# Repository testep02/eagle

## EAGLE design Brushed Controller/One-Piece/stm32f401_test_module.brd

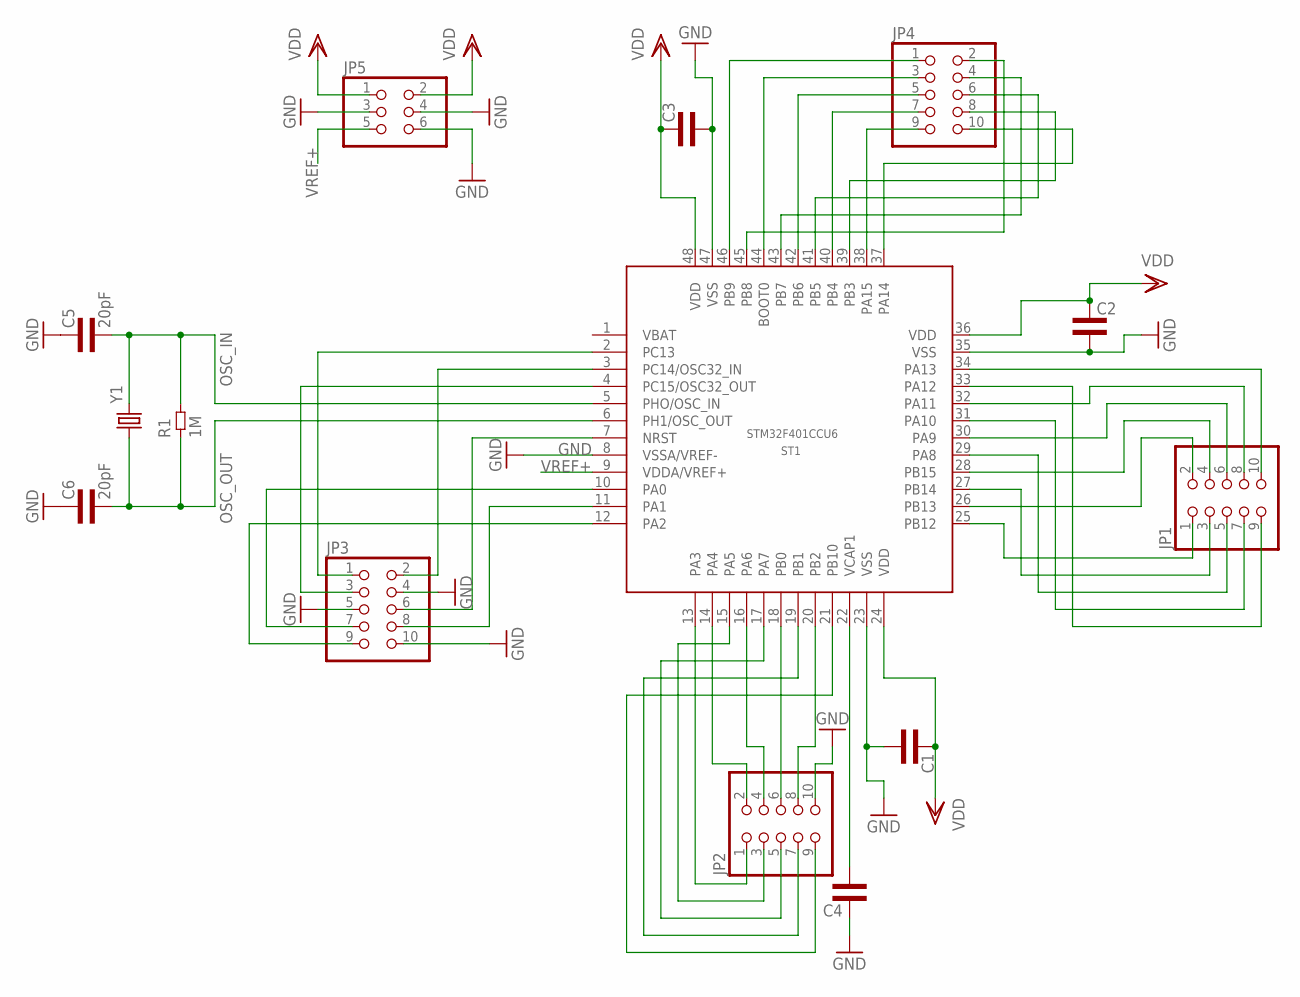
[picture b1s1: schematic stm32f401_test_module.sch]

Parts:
C1, C2, C3, C4: CAP0402L3; 0402L3
C5, C6: 20pF; 0603L3
JP1, JP2, JP3, JP4: PINHD-2X5; 2X05
JP5: PINHD-2X3; 2X03
R1: 1M; 0603L3
ST1: STM32F401CCU6; UFQFPN48
Y1: CRYSTALHC49US; HC49US

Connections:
GND: C1.P$2 (2), C2.P$2 (2), C3.P$2 (2), C4.P$1 (1), C5.P$1 (1), C6.P$1 (1), JP2.10, JP3.4, JP3.5, JP3.10, JP5.3, JP5.4, JP5.6, ST1.8 (VSSA/VREF-), ST1.23 (VSS), ST1.35 (VSS), ST1.47 (VSS)
unnamed: JP2.7, ST1.19 (PB1)
unnamed: JP2.8, ST1.20 (PB2)
unnamed: JP2.9, ST1.21 (PB10)
unnamed: C4.P$2 (2), ST1.22 (VCAP1)
unnamed: JP3.1, ST1.2 (PC13)
unnamed: JP3.2, ST1.3 (PC14/OSC32_IN)
unnamed: JP3.3, ST1.4 (PC15/OSC32_OUT)
unnamed: JP3.6, ST1.7 (NRST)
unnamed: JP3.7, ST1.10 (PA0)
unnamed: JP3.8, ST1.11 (PA1)
unnamed: JP3.9, ST1.12 (PA2)
unnamed: JP2.1, ST1.13 (PA3)
unnamed: JP2.2, ST1.14 (PA4)
unnamed: JP2.3, ST1.15 (PA5)
unnamed: JP2.4, ST1.16 (PA6)
unnamed: JP2.5, ST1.17 (PA7)
unnamed: JP2.6, ST1.18 (PB0)
unnamed: JP1.1, ST1.25 (PB12)
unnamed: JP1.2, ST1.26 (PB13)
unnamed: JP1.3, ST1.27 (PB14)
unnamed: JP1.4, ST1.28 (PB15)
unnamed: JP1.5, ST1.29 (PA8)
unnamed: JP1.6, ST1.30 (PA9)
unnamed: JP1.7, ST1.31 (PA10)
unnamed: JP1.8, ST1.32 (PA11)
unnamed: JP1.9, ST1.33 (PA12)
unnamed: JP1.10, ST1.34 (PA13)
unnamed: JP4.1, ST1.46 (PB9)
unnamed: JP4.2, ST1.45 (PB8)
unnamed: JP4.3, ST1.44 (BOOT0)
unnamed: JP4.4, ST1.43 (PB7)
unnamed: JP4.5, ST1.42 (PB6)
unnamed: JP4.6, ST1.41 (PB5)
unnamed: JP4.7, ST1.40 (PB4)
unnamed: JP4.8, ST1.39 (PB3)
unnamed: JP4.9, ST1.38 (PA15)
unnamed: JP4.10, ST1.37 (PA14)
OSC_IN: C5.P$2 (2), R1.P$2 (2), ST1.5 (PHO/OSC_IN), Y1.2
OSC_OUT: C6.P$2 (2), R1.P$1 (1), ST1.6 (PH1/OSC_OUT), Y1.1
VDD: C1.P$1 (1), C2.P$1 (1), C3.P$1 (1), JP5.1, JP5.2, ST1.24 (VDD), ST1.36 (VDD), ST1.48 (VDD)
VREF+: JP5.5, ST1.9 (VDDA/VREF+)

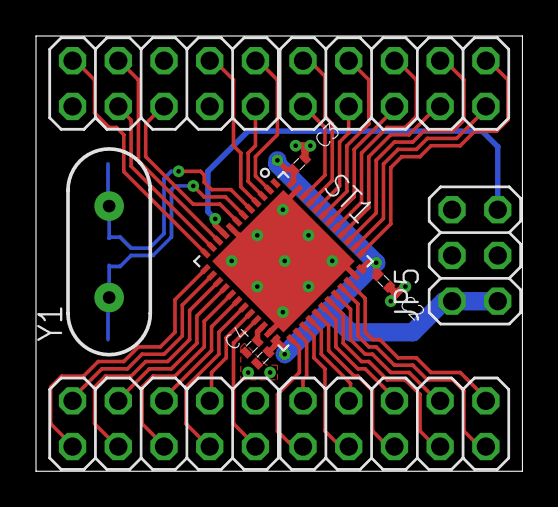
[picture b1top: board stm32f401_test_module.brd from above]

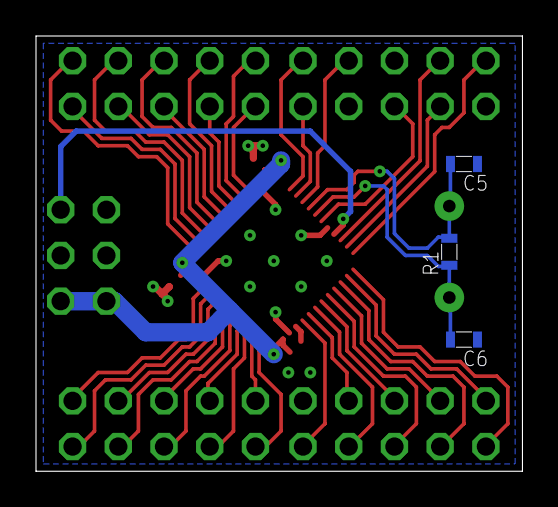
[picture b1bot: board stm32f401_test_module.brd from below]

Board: 2 copper layers, 27.0 x 24.2 mm, 14 parts (3 on the bottom side), 42 nets.

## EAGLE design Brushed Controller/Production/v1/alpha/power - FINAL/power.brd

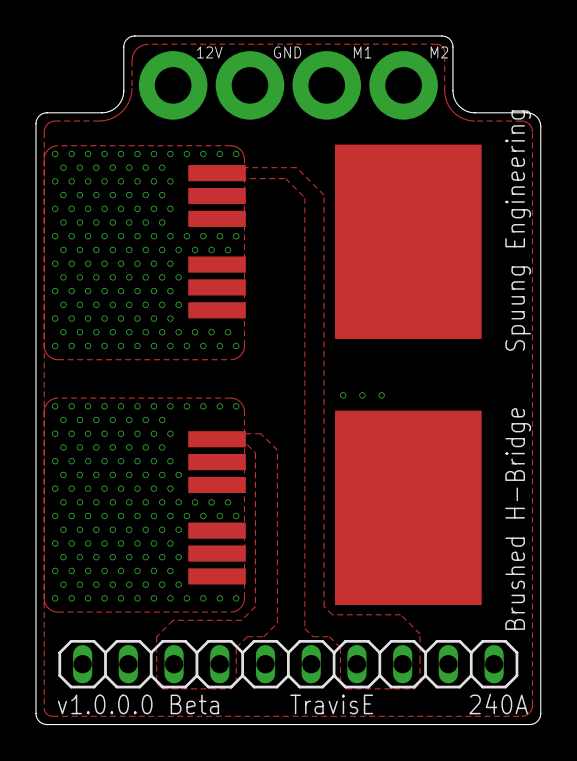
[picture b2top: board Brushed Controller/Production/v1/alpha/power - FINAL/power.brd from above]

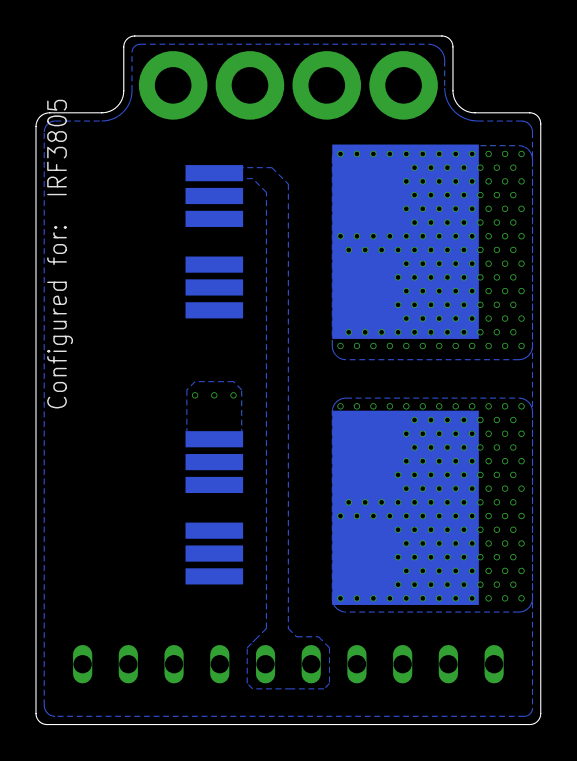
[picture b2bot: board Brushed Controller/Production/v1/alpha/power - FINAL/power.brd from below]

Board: 4 copper layers, 28.0 x 38.3 mm, 5 parts (2 on the bottom side), 8 nets, no tracks yet.

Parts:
JP1: 1X10
U$1, U$2, U$3, U$4: IRF3805STRL-7PP; D2PAK-7

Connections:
12V: U$1.8, U$2.8
GND: U$3.2, U$3.3, U$3.5, U$3.6, U$3.7, U$4.2, U$4.3, U$4.5, U$4.6, U$4.7
HO1: JP1.7, JP1.8, U$1.1
HO2: JP1.3, JP1.4, U$2.1
LO1: JP1.5, JP1.6, U$3.1
LO2: JP1.1, JP1.2, U$4.1
M1: JP1.10, U$1.2, U$1.3, U$1.5, U$1.6, U$1.7, U$3.8
M2: JP1.9, U$2.2, U$2.3, U$2.5, U$2.6, U$2.7, U$4.8

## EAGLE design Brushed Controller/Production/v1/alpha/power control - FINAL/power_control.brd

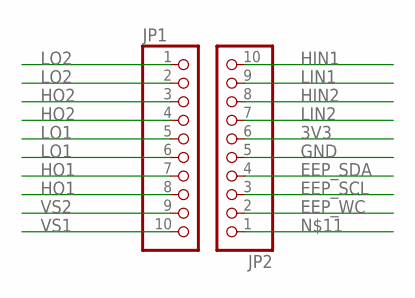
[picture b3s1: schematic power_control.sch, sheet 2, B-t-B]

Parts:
JP1, JP2: PINHD-1X10_2.54-SMD; 1X10SMD

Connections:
3V3: JP2.6; also elsewhere on the board
EEP_SCL: JP2.3; also elsewhere on the board
EEP_SDA: JP2.4; also elsewhere on the board
EEP_WC: JP2.2; also elsewhere on the board
GND: JP2.5; also elsewhere on the board
HIN1: JP2.10; also elsewhere on the board
HIN2: JP2.8; also elsewhere on the board
HO1: JP1.7, JP1.8; also elsewhere on the board
HO2: JP1.3, JP1.4; also elsewhere on the board
LIN1: JP2.9; also elsewhere on the board
LIN2: JP2.7; also elsewhere on the board
LO1: JP1.5, JP1.6; also elsewhere on the board
LO2: JP1.1, JP1.2; also elsewhere on the board
VS1: JP1.10; also elsewhere on the board
VS2: JP1.9; also elsewhere on the board

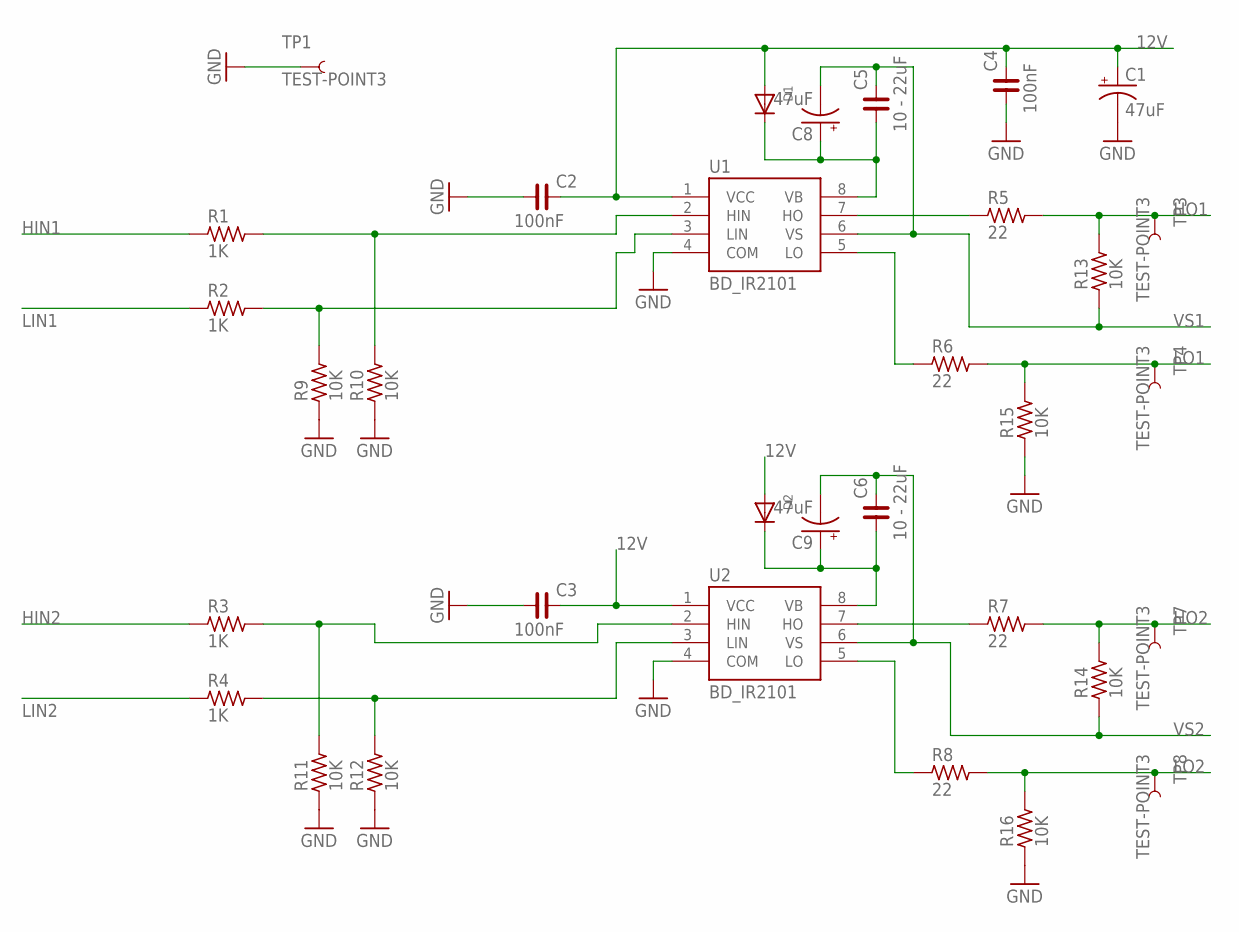
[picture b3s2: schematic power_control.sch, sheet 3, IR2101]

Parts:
C1, C8, C9: 47uF; B/3528-21W
C2, C3, C4: 100nF; C0201
C5, C6: 10 - 22uF; C0805
D1, D2: DIODESOD-523; SOD-523
R1, R2, R3, R4: 1K; R0201
R5, R6, R7, R8: 22; R0805
R9, R10, R11, R12: 10K; R0201
R13, R14, R15, R16: 10K; R0805
TP1, TP3, TP4, TP7, TP8: TEST-POINT3; PAD.03X.03
U1, U2: BD_IR2101; SO8

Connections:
12V: C1.+, C2.2, C3.2, C4.2, D1.A, D2.A, U1.1 (VCC), U2.1 (VCC)
GND: C1.-, C2.1, C3.1, C4.1, R9.1, R10.1, R11.1, R12.1, R15.1, R16.1, TP1.P$1, U1.4 (COM), U2.4 (COM); also elsewhere on the board
HIN1: R1.1; also elsewhere on the board
HIN2: R3.1; also elsewhere on the board
HO1: R5.2, R13.2, TP3.P$1; also elsewhere on the board
HO2: R7.2, R14.2, TP7.P$1; also elsewhere on the board
LIN1: R2.1; also elsewhere on the board
LIN2: R4.1; also elsewhere on the board
LO1: R6.2, R15.2, TP4.P$1; also elsewhere on the board
LO2: R8.2, R16.2, TP8.P$1; also elsewhere on the board
unnamed: C6.1, C9.+, D2.K (C), U2.8 (VB)
unnamed: C5.1, C8.+, D1.K (C), U1.8 (VB)
unnamed: R1.2, R10.2, U1.2 (HIN)
unnamed: R2.2, R9.2, U1.3 (LIN)
unnamed: R5.1, U1.7 (HO)
unnamed: R6.1, U1.5 (LO)
unnamed: R3.2, R11.2, U2.2 (HIN)
unnamed: R4.2, R12.2, U2.3 (LIN)
unnamed: R7.1, U2.7 (HO)
unnamed: R8.1, U2.5 (LO)
VS1: C5.2, C8.-, R13.1, U1.6 (VS); also elsewhere on the board
VS2: C6.2, C9.-, R14.1, U2.6 (VS); also elsewhere on the board

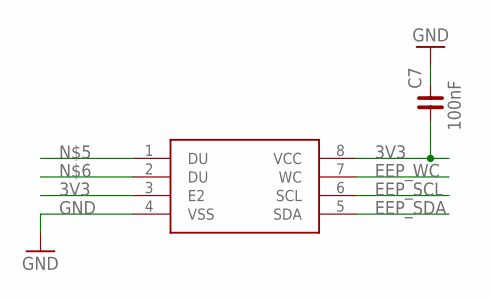
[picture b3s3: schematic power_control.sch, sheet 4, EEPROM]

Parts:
C7: 100nF; C0201
M24M02: M24M02-DRMN6TP; SO08

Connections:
3V3: C7.1, M24M02.3 (E2), M24M02.8 (VCC); also elsewhere on the board
EEP_SCL: M24M02.6 (SCL); also elsewhere on the board
EEP_SDA: M24M02.5 (SDA); also elsewhere on the board
EEP_WC: M24M02.7 (WC); also elsewhere on the board
GND: C7.2, M24M02.4 (VSS); also elsewhere on the board

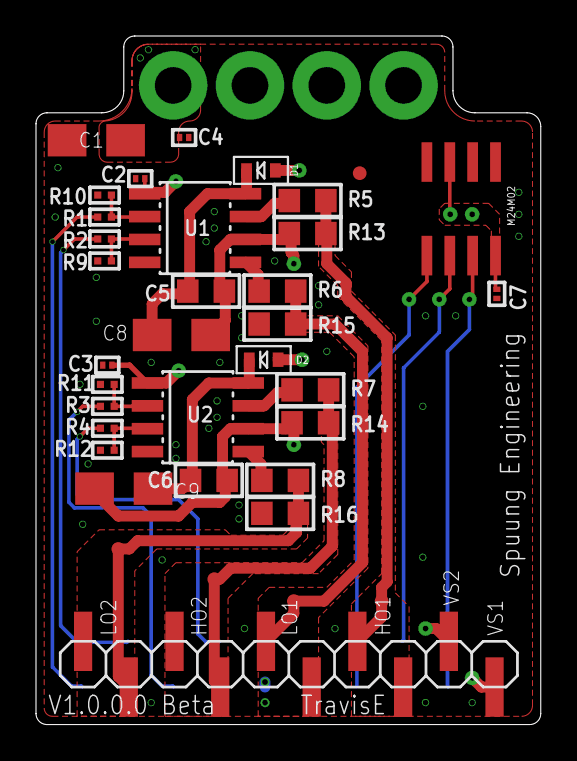
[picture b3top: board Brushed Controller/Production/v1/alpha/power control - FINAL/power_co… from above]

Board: 4 copper layers, 28.0 x 38.3 mm, 37 parts (1 on the bottom side), 26 nets.

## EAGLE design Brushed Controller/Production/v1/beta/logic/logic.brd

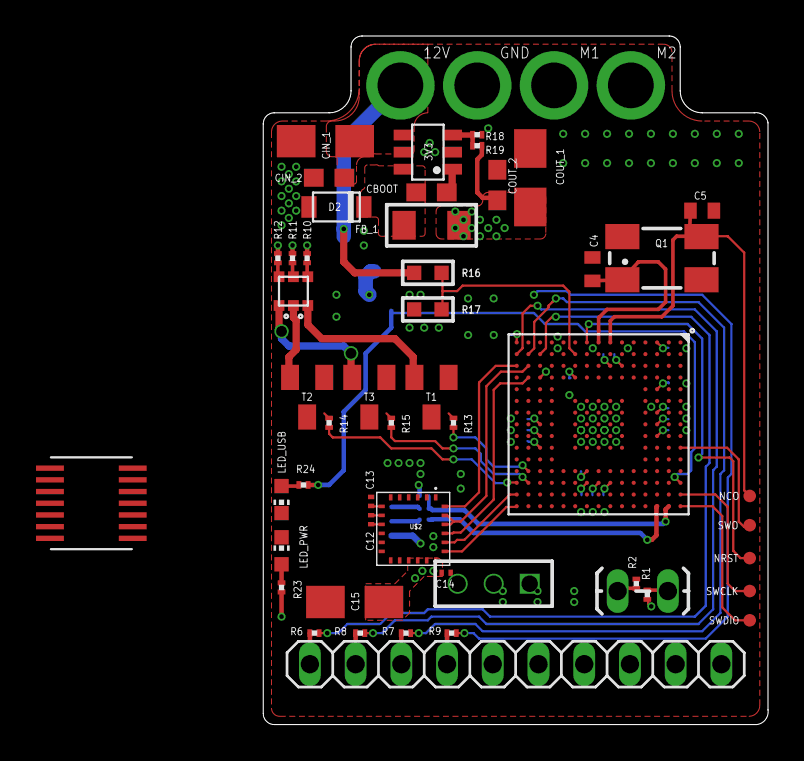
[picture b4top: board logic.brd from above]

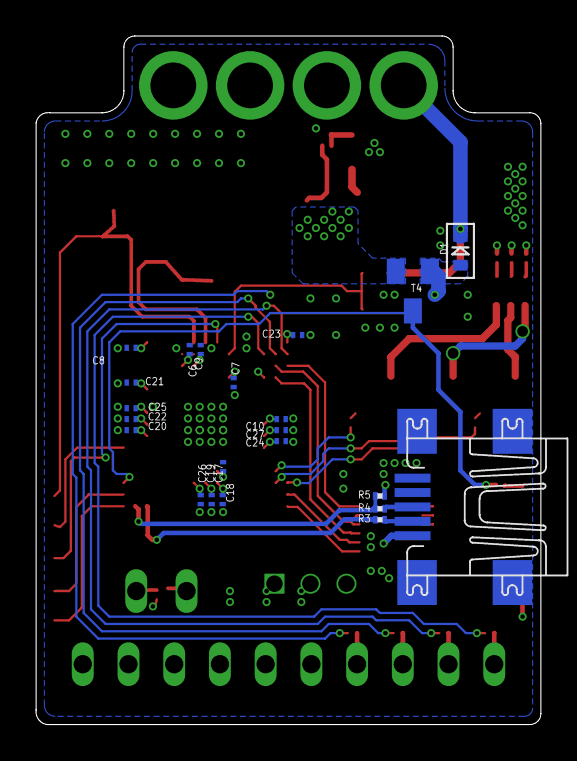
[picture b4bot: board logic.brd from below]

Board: 4 copper layers, 28.0 x 38.3 mm, 72 parts (22 on the bottom side), 51 nets.

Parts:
3V3: LMR14206; R-PDSO-G6
C4, C5: 20p; C0402
C6, C7, C8, C9, C10, C17, C18, C19, C20, C21, C22, C23, C24, C25, C26, C27: 100n; C0201
C12: .22uF; C0201
C13: 4.7uF; C0201
C14: 100nF; C0201
C15: 10uF; B/3528-21W
CBOOT: .15uF; C0603
CIN_1: 10uF; B/3528-21W
CIN_2: 100nF; C0603
COUT_1: 47uF; B/3528-21W
COUT_2: 100nF; C0603
D1: SOD-523
D2: DB2W60400L; SC-109B
FB_1: FB_1206; L1206
JP1: M02LOCK_LONGPADS; 1X02_LOCK_LONGPADS
JP2: 1X03M
JP3: 1X10
LED1: LED_RGB3; RGBLED
LED_PWR: CHIP-LED0603
LED_USB: CHIP-LED0603
NCO: TPTP07R; TP07R
NRST: TPTP07R; TP07R
Q1: CTS406
R1, R10, R11, R12, R13, R14, R15: 100; R0201
R2: 10K; R0201
R3, R4, R6, R7, R8, R9: 22; R0201
R5: 1.5K; R0201
R16, R17: R0603
R18: 1.02K; R0201
R19: 3.4K; R0201
R23, R24: 330; R0201
SWCLK: TPTP07R; TP07R
SWDIO: TPTP07R; TP07R
SWO: TPTP07R; TP07R
T1, T2, T3, T4: SOT23-BEC
U1: R-PDSO-G14
U$2: LSM9DS0; LGA-24
U$6: STM32F407IG; UFBGA176+25
X1: MINI-USB-UX60A-MB-5ST; UX60A-MB-5ST

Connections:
3V3: 3V3.6, CBOOT.2, D2.1, FB_1.1
+12V: 3V3.4, 3V3.5, CIN_1.+, CIN_2.1, D1.K, R16.2
GND: 3V3.2, C4.2, C5.2, C6.2, C7.2, C8.2, C9.2, C10.2, C13.1, C14.1, C15.-, C17.2, C18.2, C19.2, C20.2, C21.2, C22.2, C23.2, C24.2, C25.2, C26.2, C27.2, CIN_1.-, CIN_2.2, COUT_1.-, COUT_2.2, D2.2, JP2.3, LED_PWR.C, LED_USB.C, R2.2, R17.1, R18.1, T1.E, T2.E, T3.E, U$2.2, U$2.3, U$2.4, U$2.5, U$2.6, U$6.D5, U$6.D7, U$6.D8, U$6.D9, U$6.F2, U$6.F6, U$6.F7, U$6.F8, U$6.F9, U$6.F10, U$6.F12, U$6.G2, U$6.G6, U$6.G7, U$6.G8, U$6.G9, U$6.G10, U$6.G12, U$6.H6, U$6.H7, U$6.H8, U$6.H9, U$6.H10, U$6.H12, U$6.J6, U$6.J7, U$6.J8, U$6.J9, U$6.J10, U$6.K6, U$6.K7, U$6.K8, U$6.K9, U$6.K10, U$6.M1, U$6.M8, U$6.M9, X1.5
HIN1: JP3.1, R6.2
HIN2: JP3.3, R7.2
LED_BLUE: R15.2, U$6.P13
LED_GREEN: R13.2, U$6.P12
LED_RED: R14.2, U$6.R13
LIN1: JP3.2, R8.2
LIN2: JP3.4, R9.2
LIPO_ADC_SIG: R16.1, R17.2, U$6.K2
unnamed: JP1.1, R1.2
unnamed: R13.1, T1.B
unnamed: R14.1, T2.B
unnamed: R15.1, T3.B
unnamed: LED1.AR, R11.2
unnamed: LED1.CR, T2.C
unnamed: 3V3.1, CBOOT.1
unnamed: JP1.2, R2.1
unnamed: R3.1, X1.2
unnamed: 3V3.3, R18.2, R19.2
unnamed: R4.1, X1.3
unnamed: C13.2, U$2.7
unnamed: C12.1, U$2.8
unnamed: LED1.CG, T1.C
unnamed: LED1.AG, R10.2
unnamed: LED1.CB, T3.C
unnamed: LED1.AB, R12.2
unnamed: C12.2, U$2.9
unnamed: LED_PWR.A, R23.1
unnamed: LED_USB.A, R24.2
NRST: NRST.TP, U$6.J1
OSC_IN: C5.1, NCO.TP, Q1.3, U$6.G1
OSC_OUT: C4.1, Q1.1, U$6.H1
PA3: R8.1, U$6.R2
PA4: R9.1, U$6.N4
PB14: U$2.20, U$6.R14
PB15: U$2.19, U$6.R15
PWM_1: R6.1, U$6.N2
PWM_2: R7.1, U$6.P2
SPI1_MISO: U$2.22, U$2.23, U$6.P3
SPI1_MOSI: U$2.24, U$6.R3
SPI1_SCK: U$2.21, U$6.P4
SWCLK: SWCLK.TP, U$6.A14
SWDIO: SWDIO.TP, U$6.A15
SWO: SWO.TP, U$6.A10
USB_DETECT: R24.1, T4.C, U$6.A13
USB_DETECT_TRANS: D1.A, T4.B, X1.1
USB_DM: R3.2, U$6.C15
USB_DP: R4.2, R5.1, U$6.B15
VDD: C6.1, C7.1, C8.1, C9.1, C10.1, C14.2, C15.+, C17.1, C18.1, C19.1, C20.1, C21.1, C22.1, C23.1, C24.1, C25.1, C26.1, C27.1, COUT_1.+, COUT_2.1, FB_1.2, JP2.2, R1.1, R5.2, R10.1, R11.1, R12.1, R19.1, R23.2, T4.E, U$2.15, U$2.16, U$2.17, U$2.18, U$6.C1, U$6.C5, U$6.C7, U$6.C8, U$6.C9, U$6.F3, U$6.G3, U$6.G13, U$6.H13, U$6.J12, U$6.J13, U$6.K4, U$6.N8, U$6.N9, U$6.N10, U$6.R1

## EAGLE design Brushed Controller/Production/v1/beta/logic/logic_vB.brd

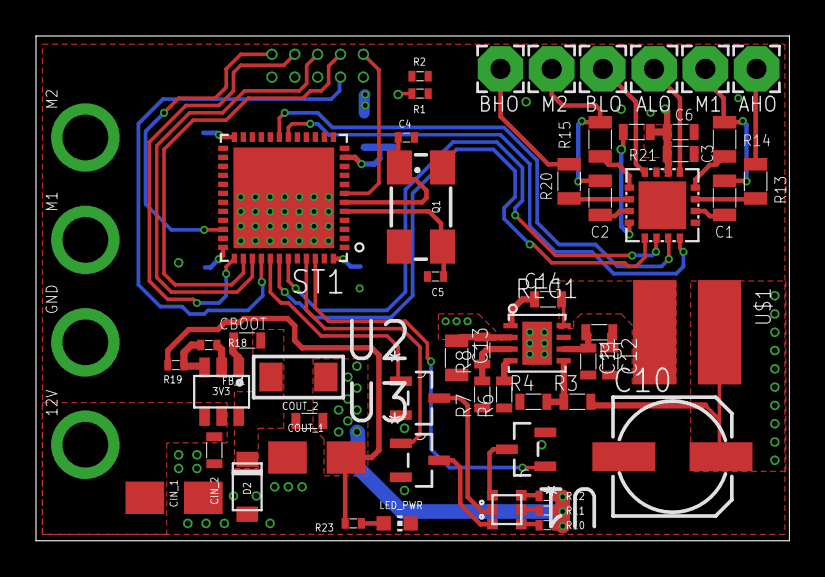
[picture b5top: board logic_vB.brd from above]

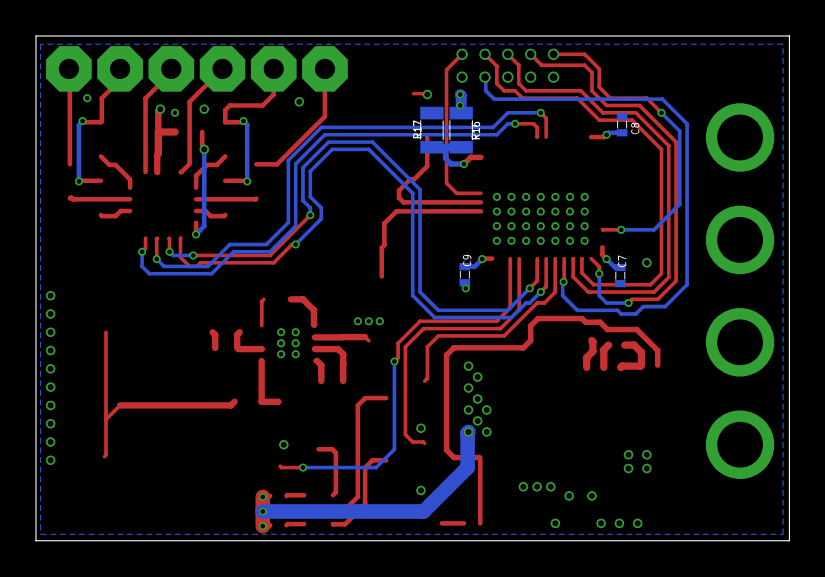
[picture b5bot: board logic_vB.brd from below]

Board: 4 copper layers, 41.9 x 28.0 mm, 59 parts (5 on the bottom side), 44 nets.

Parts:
3V3: LMR14206; R-PDSO-G6
AHO: 2,54/1,1
ALO: 2,54/1,1
BHO: 2,54/1,1
BLO: 2,54/1,1
C1, C2: 10u; 0805L3
C3: 1u; 0603L3
C4, C5: 20p; 0402L3
C6: 10u; 0603L3
C7, C8, C9: 100n; 0402L3
C10: 153CLV-0605
C11, C12, C14: 0603L3
C13: 0805L3
CBOOT: .15uF; 0603L3
CIN_1: 10uF; B/3528-21W
CIN_2: 100nF; 0603L3
COUT_1: 47uF; B/3528-21W
COUT_2: 100nF; 0603L3
D2: DB2W60400L; SC-109B
FB_1: FB_1206; L1206
LED1: LED_RGB3; RGBLED
LED_PWR: CHIP-LED0603
M1, M2: 2,54/1,1
MD1: QFN44-16LD-PL-2
Q1: CTS406
R1: 100; 0402L3
R2: 10K; 0402L3
R3, R4, R5, R6, R7, R8: 0603L3
R10, R23: 330; 0402L3
R11: 1K; 0402L3
R12: 510; 0402L3
R13, R20: 10R; 0805L3
R14, R15: 2R; 0805L3
R16, R17: 0805L3
R18: 1.02K; 0402L3
R19: 3.4K; 0402L3
R21: 100K; 0603L3
REG1: S-PVSON-N8
ST1: UFQFPN48
U1, U2, U3: BC817-25; SOT95P240X97-3N
U$1: SDR0604

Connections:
3V3: 3V3.6, CBOOT.P$2, D2.1, FB_1.1
+12V: 3V3.4, 3V3.5, C13.1, CIN_1.+, CIN_2.P$1, R8.P$2, R16.2, REG1.2
AB: LED1.AB, R12.P$2
AG: LED1.AG, R10.P$2
AHO: AHO.1, R13.2
ALO: ALO.1, MD1.5
AR: LED1.AR, R11.P$2
BHO: BHO.1, R20.2
BLO: BLO.1, MD1.8
BOOT: C14.P$1, REG1.1
COMP: C11.P$1, R5.P$2, REG1.6
EN: R7.P$2, R8.P$1, REG1.3
GND: 3V3.2, C3.P$1, C4.P$2, C5.P$2, C6.P$1, C7.P$2, C8.P$2, C9.P$2, C10.-, C11.P$2, C12.P$2, C13.2, CIN_1.-, CIN_2.P$2, COUT_1.-, COUT_2.P$2, D2.2, LED_PWR.C, MD1.7, MD1.TP, R2.P$2, R4.P$1, R6.P$1, R7.P$1, R17.1, R18.P$1, REG1.7, REG1.P$1, ST1.23, ST1.35, ST1.47, U1.2, U2.2, U3.2
LED_BLUE: ST1.16, ST1.46, U1.1
LED_GREEN: ST1.15, ST1.45, U3.1
LED_RED: ST1.41, U2.1
LIPO_ADC_SIG: R16.1, R17.2, ST1.11
M1: C1.1, M1.1, R14.2
M2: C2.1, M2.1, R15.2
unnamed: C1.2, MD1.2
unnamed: C2.2, MD1.11
unnamed: MD1.3, R13.1
unnamed: 3V3.1, CBOOT.P$1
unnamed: MD1.4, R14.1
unnamed: MD1.9, R15.1
unnamed: MD1.10, R20.1
unnamed: 3V3.3, R18.P$2, R19.P$2
unnamed: LED1.CG, U3.3
unnamed: LED1.CR, U2.3
unnamed: LED1.CB, U1.3
unnamed: C12.P$1, R5.P$1
unnamed: LED_PWR.A, R23.P$1
unnamed: MD1.12, R21.P$1
OSC_IN: C5.P$1, Q1.3, ST1.5
OSC_OUT: C4.P$1, Q1.1, ST1.6
PH: C14.P$2, REG1.8, U$1.2
PWM_1: MD1.16, ST1.18
PWM_2: MD1.15, ST1.19
PWM_3: MD1.13, ST1.42
PWM_4: MD1.14, ST1.43
RT: R6.P$2, REG1.4
VCC: C3.P$2, C6.P$2, C10.+, MD1.6, R3.P$2, R21.P$2, U$1.1
VDD: C7.P$1, C8.P$1, C9.P$1, COUT_1.+, COUT_2.P$1, FB_1.2, R1.P$1, R10.P$1, R11.P$1, R12.P$1, R19.P$1, R23.P$2, ST1.24, ST1.36, ST1.48
VSENSE: R3.P$1, R4.P$2, REG1.5

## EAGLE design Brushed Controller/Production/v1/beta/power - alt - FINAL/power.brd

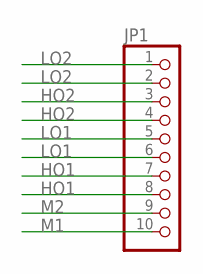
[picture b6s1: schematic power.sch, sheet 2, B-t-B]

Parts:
JP1: PINHD-1X10_2.54; 1X10

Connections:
HO1: JP1.7, JP1.8; also elsewhere on the board
HO2: JP1.3, JP1.4; also elsewhere on the board
LO1: JP1.5, JP1.6; also elsewhere on the board
LO2: JP1.1, JP1.2; also elsewhere on the board
M1: JP1.10; also elsewhere on the board
M2: JP1.9; also elsewhere on the board

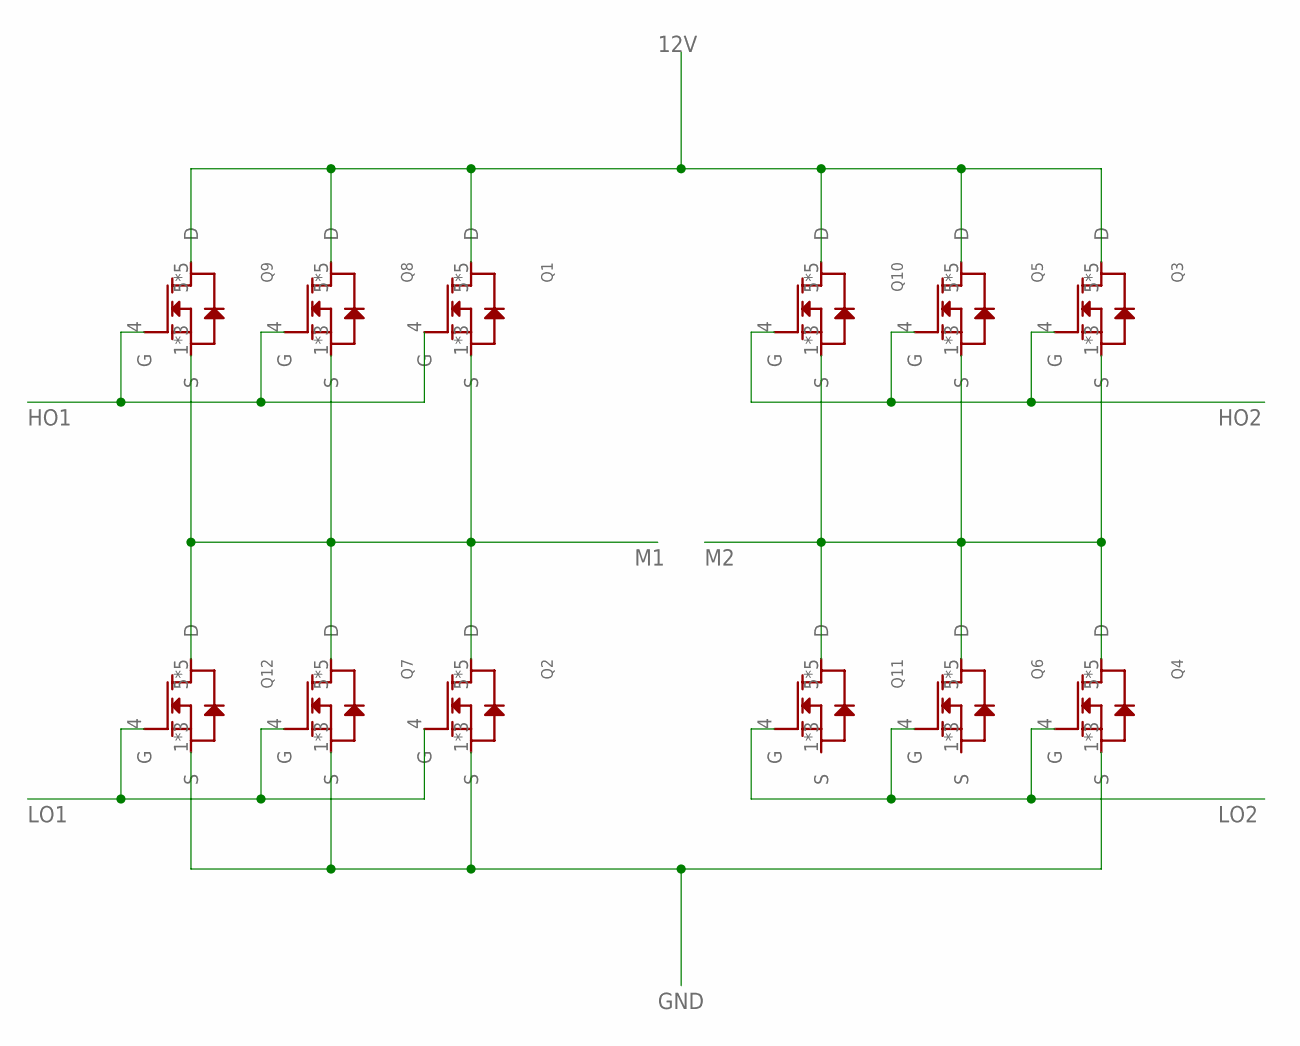
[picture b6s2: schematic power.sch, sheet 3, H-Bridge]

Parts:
Q1, Q2, Q3, Q4, Q5, Q6, Q7, Q8, Q9, Q10, Q11, Q12: CSD18540Q5B; Q5B

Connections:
12V: Q1.5 (D), Q1.6 (D), Q1.7 (D), Q1.8 (D), Q1.9 (D), Q3.5 (D), Q3.6 (D), Q3.7 (D), Q3.8 (D), Q3.9 (D), Q5.5 (D), Q5.6 (D), Q5.7 (D), Q5.8 (D), Q5.9 (D), Q8.5 (D), Q8.6 (D), Q8.7 (D), Q8.8 (D), Q8.9 (D), Q9.5 (D), Q9.6 (D), Q9.7 (D), Q9.8 (D), Q9.9 (D), Q10.5 (D), Q10.6 (D), Q10.7 (D), Q10.8 (D), Q10.9 (D)
GND: Q2.1 (S), Q2.2 (S), Q2.3 (S), Q4.1 (S), Q4.2 (S), Q4.3 (S), Q7.1 (S), Q7.2 (S), Q7.3 (S), Q12.1 (S), Q12.2 (S), Q12.3 (S)
HO1: Q1.4 (G), Q8.4 (G), Q9.4 (G); also elsewhere on the board
HO2: Q3.4 (G), Q5.4 (G), Q10.4 (G); also elsewhere on the board
LO1: Q2.4 (G), Q7.4 (G), Q12.4 (G); also elsewhere on the board
LO2: Q4.4 (G), Q6.4 (G), Q11.4 (G); also elsewhere on the board
M1: Q1.1 (S), Q1.2 (S), Q1.3 (S), Q2.5 (D), Q2.6 (D), Q2.7 (D), Q2.8 (D), Q2.9 (D), Q7.5 (D), Q7.6 (D), Q7.7 (D), Q7.8 (D), Q7.9 (D), Q8.1 (S), Q8.2 (S), Q8.3 (S), Q9.1 (S), Q9.2 (S), Q9.3 (S), Q12.5 (D), Q12.6 (D), Q12.7 (D), Q12.8 (D), Q12.9 (D); also elsewhere on the board
M2: Q3.1 (S), Q3.2 (S), Q3.3 (S), Q4.5 (D), Q4.6 (D), Q4.7 (D), Q4.8 (D), Q4.9 (D), Q5.1 (S), Q5.2 (S), Q5.3 (S), Q6.5 (D), Q6.6 (D), Q6.7 (D), Q6.8 (D), Q6.9 (D), Q10.1 (S), Q10.2 (S), Q10.3 (S), Q11.5 (D), Q11.6 (D), Q11.7 (D), Q11.8 (D), Q11.9 (D); also elsewhere on the board

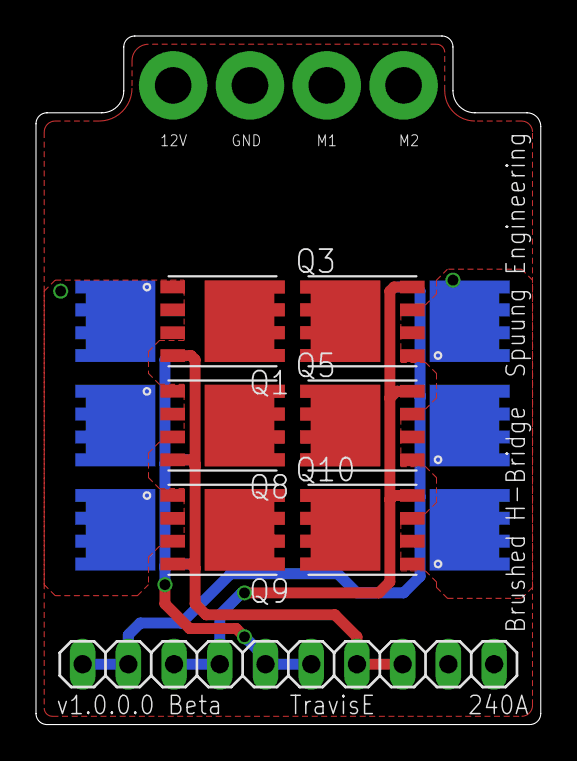
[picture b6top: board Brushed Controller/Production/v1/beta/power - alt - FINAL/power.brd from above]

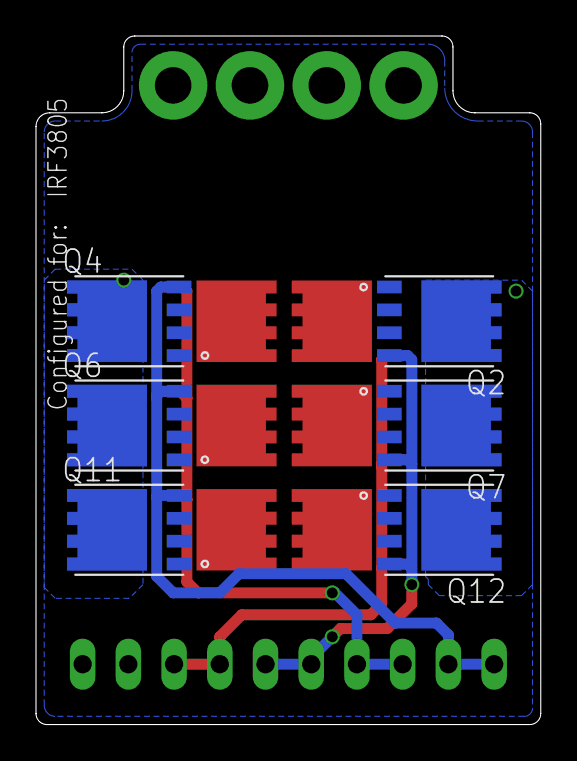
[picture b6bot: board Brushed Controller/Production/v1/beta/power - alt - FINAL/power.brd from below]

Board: 4 copper layers, 28.0 x 38.3 mm, 13 parts (6 on the bottom side), 8 nets.

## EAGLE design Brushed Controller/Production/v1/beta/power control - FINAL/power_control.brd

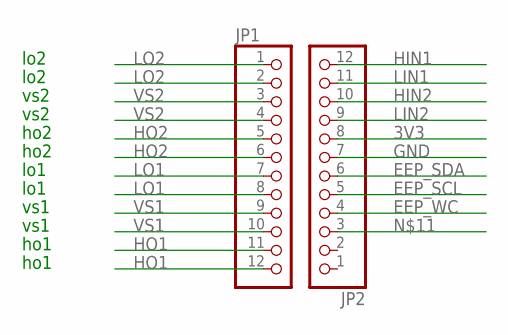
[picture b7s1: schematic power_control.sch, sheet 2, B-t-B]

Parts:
JP1, JP2: PINHD-1X12_2.54-SMD; 1X12SMD

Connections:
3V3: JP2.8; also elsewhere on the board
EEP_SCL: JP2.5; also elsewhere on the board
EEP_SDA: JP2.6; also elsewhere on the board
EEP_WC: JP2.4; also elsewhere on the board
GND: JP2.7; also elsewhere on the board
HIN1: JP2.12; also elsewhere on the board
HIN2: JP2.10; also elsewhere on the board
HO1: JP1.11, JP1.12; also elsewhere on the board
HO2: JP1.5, JP1.6; also elsewhere on the board
LIN1: JP2.11; also elsewhere on the board
LIN2: JP2.9; also elsewhere on the board
LO1: JP1.7, JP1.8; also elsewhere on the board
LO2: JP1.1, JP1.2; also elsewhere on the board
VS1: JP1.9, JP1.10; also elsewhere on the board
VS2: JP1.3, JP1.4; also elsewhere on the board

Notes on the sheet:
lo2
vs2
ho2
lo1
vs1
ho1

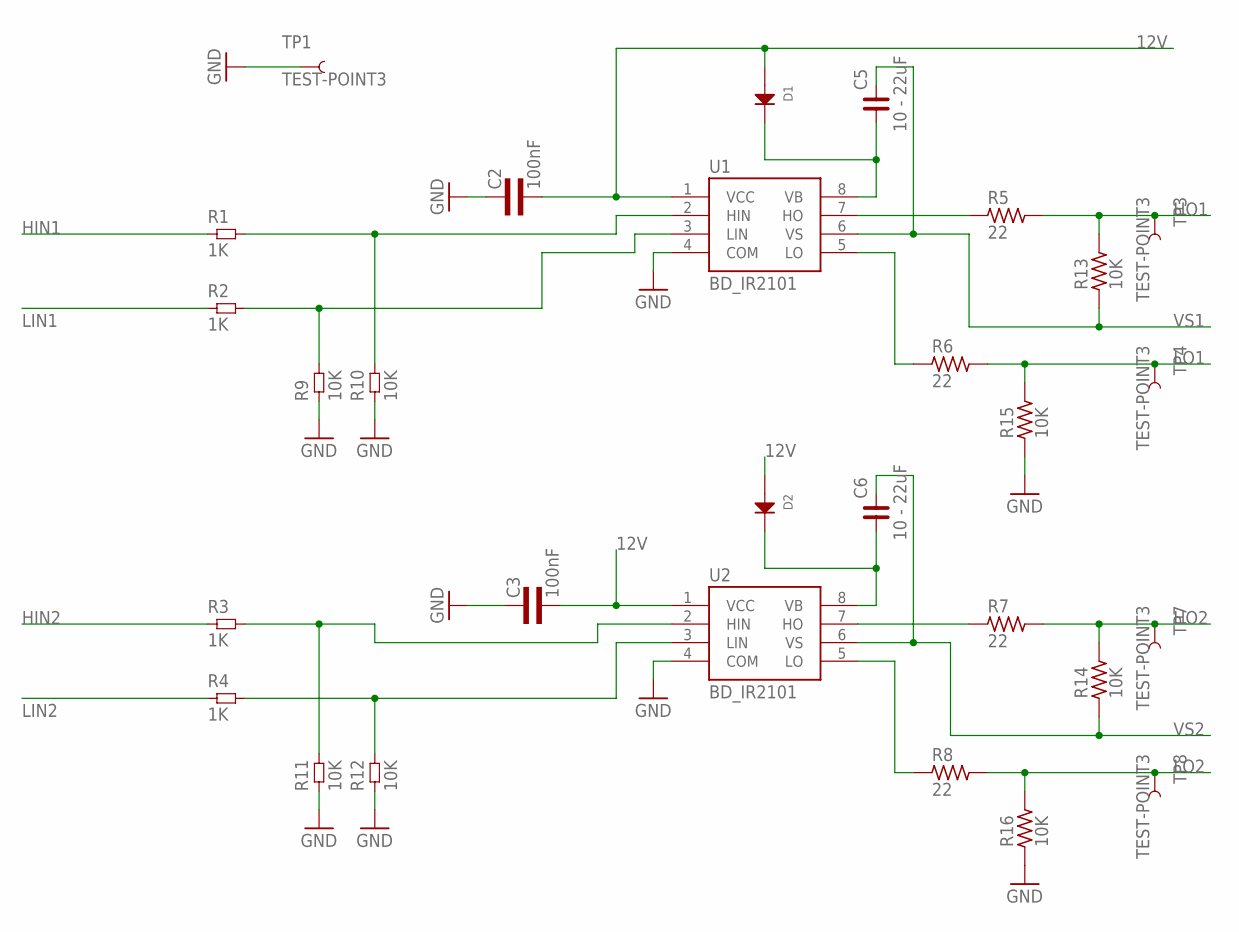
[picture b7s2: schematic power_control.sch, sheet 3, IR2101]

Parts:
C2, C3: 100nF; 0603L3
C5, C6: 10 - 22uF; C0805
D1, D2: DIODETMINIP2-F2-B; TMINIP2-F2-B; PARTNUM DB2441600L
R1, R2, R3, R4: 1K; 0603L3
R5, R6, R7, R8: 22; R0805
R9, R10, R11, R12: 10K; 0603L3
R13, R14, R15, R16: 10K; R0805
TP1, TP3, TP4, TP7, TP8: TEST-POINT3; PAD.03X.03
U1, U2: BD_IR2101; SO8

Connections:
12V: C2.P$2 (2), C3.P$2 (2), D1.2 (ANODE), D2.2 (ANODE), U1.1 (VCC), U2.1 (VCC); also elsewhere on the board
GND: C2.P$1 (1), C3.P$1 (1), R9.P$1 (1), R10.P$1 (1), R11.P$1 (1), R12.P$1 (1), R15.1, R16.1, TP1.P$1, U1.4 (COM), U2.4 (COM); also elsewhere on the board
HIN1: R1.P$1 (1); also elsewhere on the board
HIN2: R3.P$1 (1); also elsewhere on the board
HO1: R5.2, R13.2, TP3.P$1; also elsewhere on the board
HO1_OUT: R5.1, U1.7 (HO)
HO2: R7.2, R14.2, TP7.P$1; also elsewhere on the board
HO2_OUT: R7.1, U2.7 (HO)
LIN1: R2.P$1 (1); also elsewhere on the board
LIN2: R4.P$1 (1); also elsewhere on the board
LO1: R6.2, R15.2, TP4.P$1; also elsewhere on the board
LO2: R8.2, R16.2, TP8.P$1; also elsewhere on the board
unnamed: R1.P$2 (2), R10.P$2 (2), U1.2 (HIN)
unnamed: R2.P$2 (2), R9.P$2 (2), U1.3 (LIN)
unnamed: R6.1, U1.5 (LO)
unnamed: R3.P$2 (2), R11.P$2 (2), U2.2 (HIN)
unnamed: R4.P$2 (2), R12.P$2 (2), U2.3 (LIN)
unnamed: R8.1, U2.5 (LO)
VB1: C5.1, D1.1 (CATHODE), U1.8 (VB)
VB2: C6.1, D2.1 (CATHODE), U2.8 (VB)
VS1: C5.2, R13.1, U1.6 (VS); also elsewhere on the board
VS2: C6.2, R14.1, U2.6 (VS); also elsewhere on the board

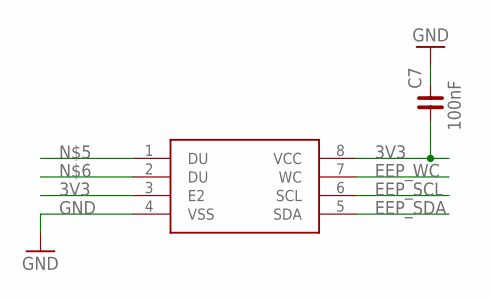
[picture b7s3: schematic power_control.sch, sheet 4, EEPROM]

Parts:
C7: 100nF; C0201
M24M02: M24M02-DRMN6TP; SO08

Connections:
3V3: C7.1, M24M02.3 (E2), M24M02.8 (VCC); also elsewhere on the board
EEP_SCL: M24M02.6 (SCL); also elsewhere on the board
EEP_SDA: M24M02.5 (SDA); also elsewhere on the board
EEP_WC: M24M02.7 (WC); also elsewhere on the board
GND: C7.2, M24M02.4 (VSS); also elsewhere on the board

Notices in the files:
parts and their libraries:
SparkFun-FreqCtrl: Licensing: CC v3.0 Share-Alike You are welcome to use this library for commercial purposes.
rc-master-smd: Copyright (C) 2007, Bob Starr
